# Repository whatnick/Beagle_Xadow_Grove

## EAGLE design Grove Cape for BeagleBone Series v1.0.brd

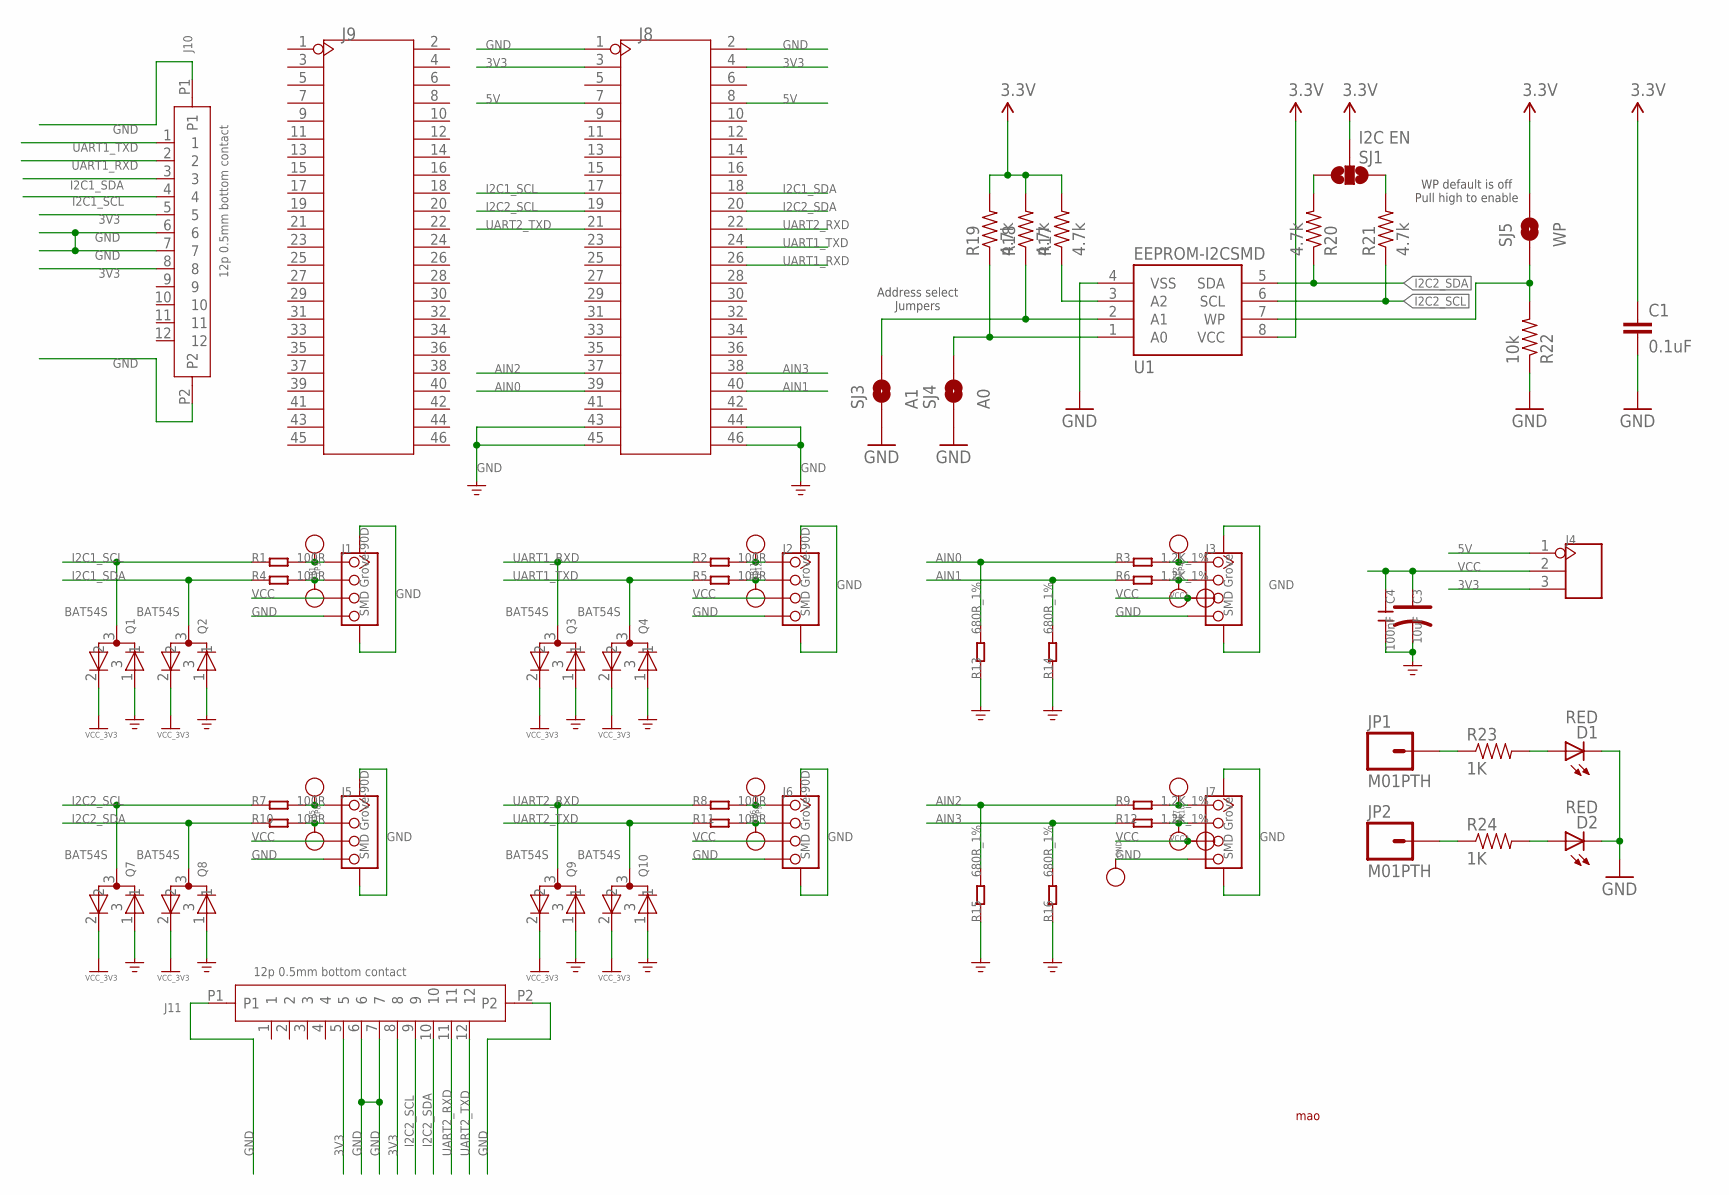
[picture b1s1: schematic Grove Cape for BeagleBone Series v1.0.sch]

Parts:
C1: 0.1uF; 0603-CAP
C3: 10uF; AVX-A
C4: 100nF; C0603
D1, D2: RED; LED-0603
GND: PAD-TEST-POINT'4545'; TP_4545
J1, J2, J5, J6: SMD Grove-90D; 4P-SMD-2.0
J3, J7: SMD Grove; 4P-SMD-2.0
J4: HEADER-3P-2.54; 3P-2.54
J8, J9: HEADER-2X23P; 2X23P-2.54
J10, J11: 12p 0.5mm bottom contact; 12P-0.5
JP1, JP2: M01PTH; 1X01
Q1, Q2, Q3, Q4, Q7, Q8, Q9, Q10: BAT54S; SOT23
R1, R2, R4, R5, R7, R8, R10, R11: 100R; R0603
R3, R6, R9, R12: 1.2K_1%; R0603
R13, R14, R15, R16: 680R_1%; R0603
R17, R18, R19, R20, R21: 4.7k; 0603
R22: 10k; 0603-RES
R23, R24: 1K; 0603-RES
SJ1: I2C EN; SJ_3_PASTE1&2&3
SJ3: A1; SJ_2S-NO
SJ4: A0; SJ_2S-NO
SJ5: WP; SJ_2S-NO
TP1, TP2, TP3, TP4, TP5, TP6, TP7, TP8, TP9, TP10, TP11, TP12: PAD-TEST-POINT'4545'; TP_4545
U1: EEPROM-I2CSMD; SO08
VCC1, VCC2: PAD-TEST-POINT'4545'; TP_4545

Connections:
3V3: C1.1, J4.3, J8.3, J8.4, J10.5, J10.8, J11.5, J11.8, Q1.2, Q2.2, Q3.2, Q4.2, Q7.2, Q8.2, Q9.2, Q10.2, R17.2, R18.2, R19.2, SJ1.2, SJ5.2, U1.8 (VCC)
5V: J4.1, J8.7, J8.8
A0: R19.1, SJ4.2, U1.1 (A0)
A1: R18.1, SJ3.2, U1.2 (A1)
AIN0: J8.39, R3.1, R13.2
AIN1: J8.40, R6.1, R14.2
AIN2: J8.37, R9.1, R15.2
AIN3: J8.38, R12.1, R16.2
GND: C1.2, C3.-, C4.2, D1.C, D2.C, GND.T, J1.4, J1.SS1, J1.SS2, J2.4, J2.SS1, J2.SS2, J3.4, J3.SS1, J3.SS2, J5.4, J5.SS1, J5.SS2, J6.4, J6.SS1, J6.SS2, J7.4, J7.SS1, J7.SS2, J8.1, J8.2, J8.43, J8.44, J8.45, J8.46, J10.6, J10.7, J10.P1, J10.P2, J11.6, J11.7, J11.P1, J11.P2, Q1.1, Q2.1, Q3.1, Q4.1, Q7.1, Q8.1, Q9.1, Q10.1, R13.1, R14.1, R15.1, R16.1, R22.1, SJ3.1, SJ4.1, U1.4 (VSS)
I2C1_SCL: J8.17, J10.4, Q1.3, R1.1
I2C1_SDA: J8.18, J10.3, Q2.3, R4.1
I2C2_SCL: J8.19, J11.9, Q7.3, R7.1, R21.1, U1.6 (SCL)
I2C2_SDA: J8.20, J11.10, Q8.3, R10.1, R20.1, U1.5 (SDA)
unnamed: R17.1, U1.3 (A2)
unnamed: J7.1, R9.2, TP7.T
unnamed: J7.2, R12.2, TP10.T
unnamed: J1.1, R1.2, TP1.T
unnamed: J1.2, R4.2, TP3.T
unnamed: J2.1, R2.2, TP11.T
unnamed: J2.2, R5.2, TP12.T
unnamed: J5.1, R7.2, TP5.T
unnamed: J5.2, R10.2, TP8.T
unnamed: J6.1, R8.2, TP6.T
unnamed: J6.2, R11.2, TP9.T
unnamed: J3.1, R3.2, TP2.T
unnamed: J3.2, R6.2, TP4.T
unnamed: R20.2, SJ1.3
unnamed: R21.2, SJ1.1
unnamed: R22.2, SJ5.1, U1.7 (WP)
unnamed: D1.A, R23.2
unnamed: D2.A, R24.2
unnamed: JP1.1, R23.1
unnamed: JP2.1, R24.1
UART1_RXD: J8.26, J10.2, Q3.3, R2.1
UART1_TXD: J8.24, J10.1, Q4.3, R5.1
UART2_RXD: J8.22, J11.11, Q9.3, R8.1
UART2_TXD: J8.21, J11.12, Q10.3, R11.1
VCC: C3.+, C4.1, J1.3, J2.3, J3.3, J4.2, J5.3, J6.3, J7.3, VCC1.T, VCC2.T

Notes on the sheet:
mao
WP default is off Pull high to enable
Address select Jumpers

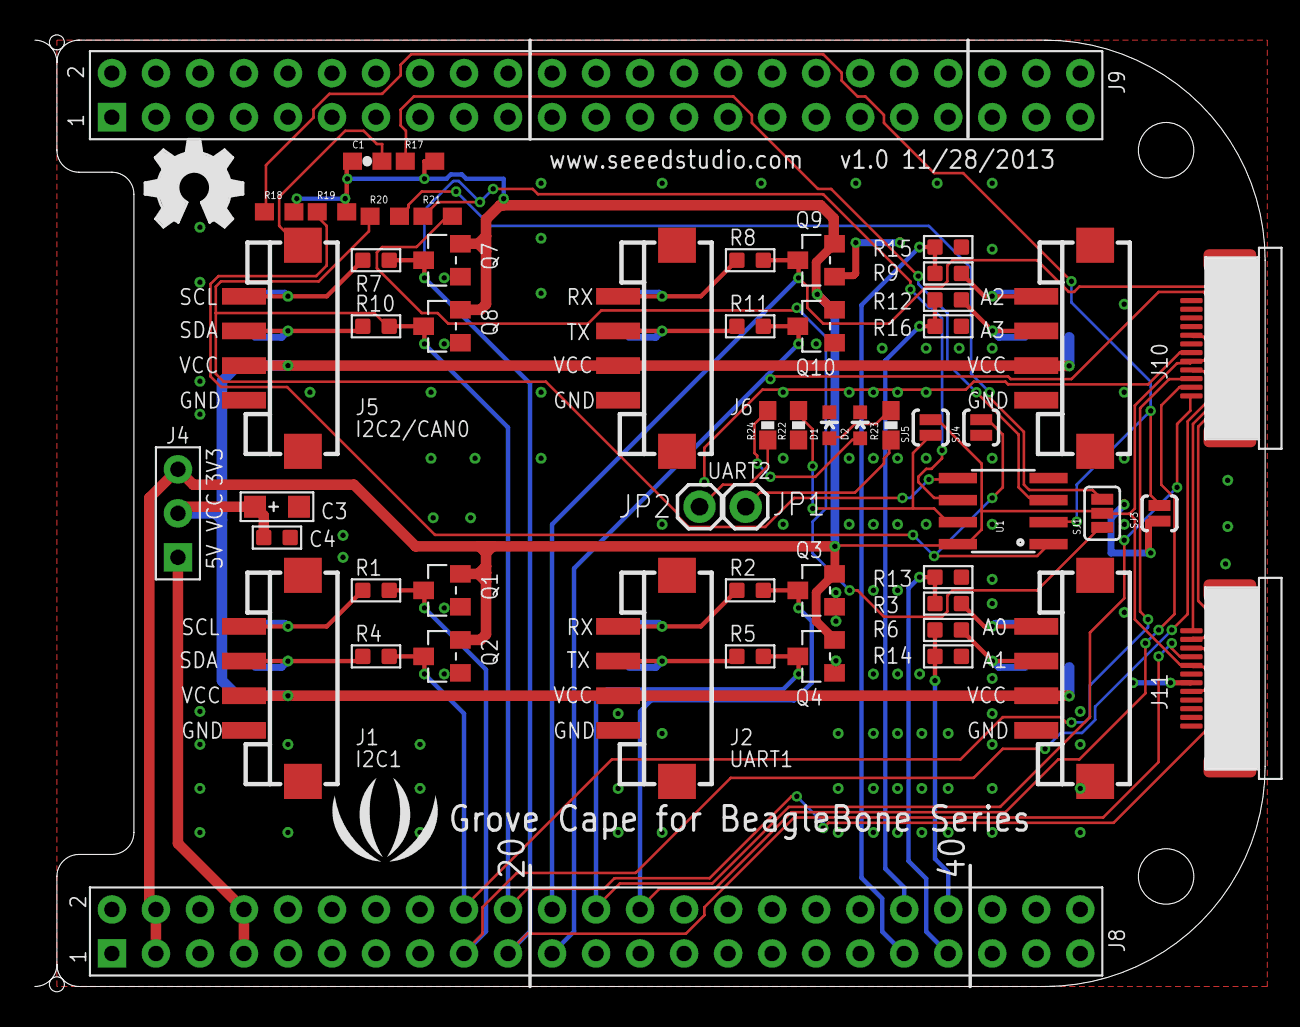
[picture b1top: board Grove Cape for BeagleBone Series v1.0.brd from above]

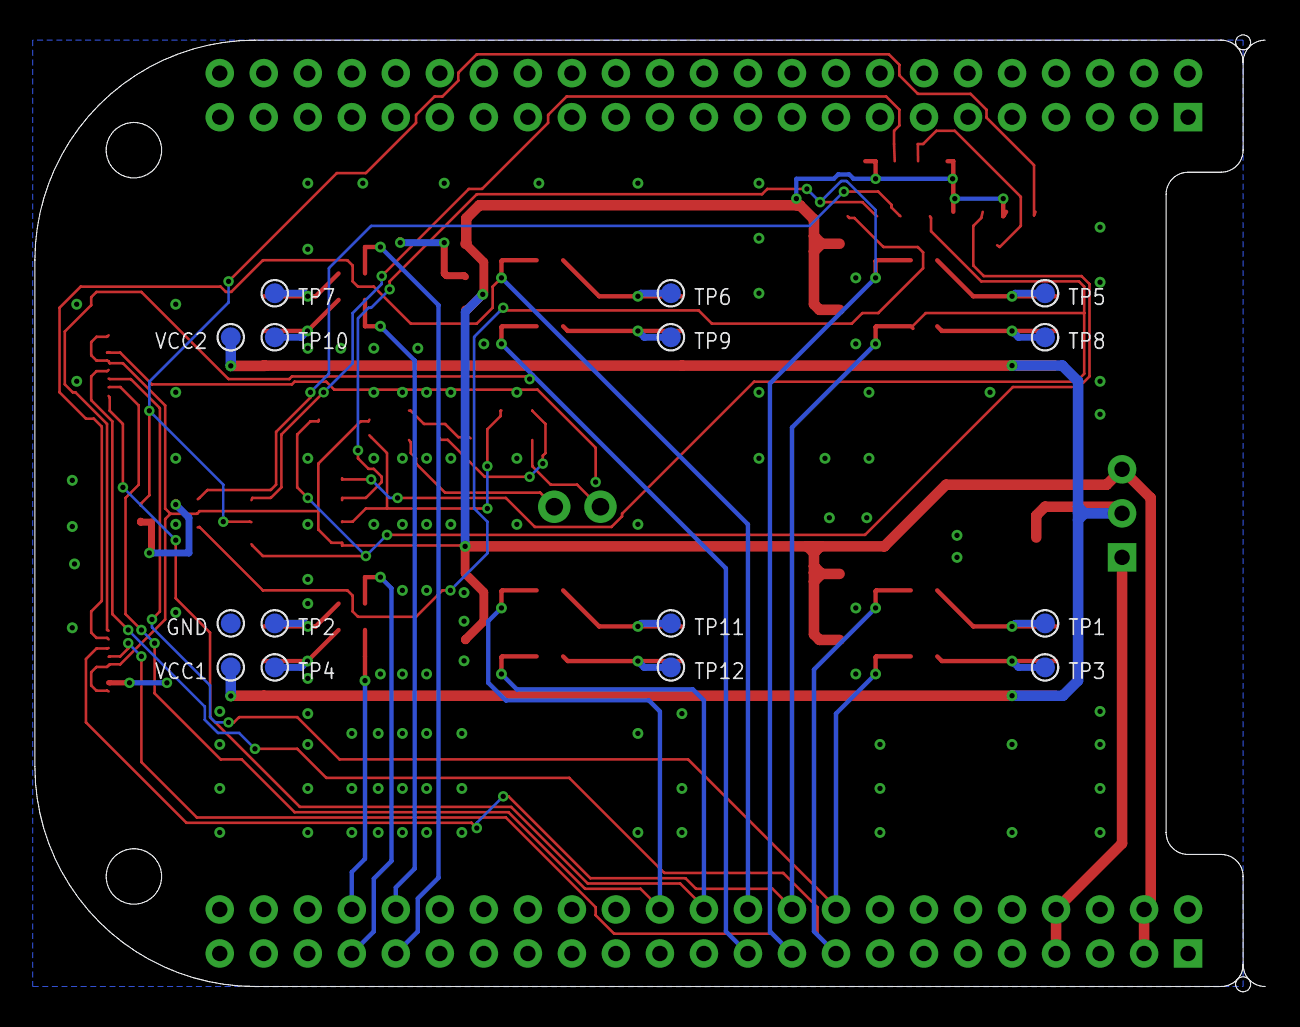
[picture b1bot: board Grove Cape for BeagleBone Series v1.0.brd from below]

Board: 2 copper layers, 71.0 x 55.2 mm, 74 parts (15 on the bottom side), 38 nets.

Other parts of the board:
U$26, U$27: HOLE-3.2/7.0
U$29: LOGO_SILK
U$33: OSHW_FILLX200_NOTEXT

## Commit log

2014-11-05 Initial import
2014-12-04 Fixed component position and silk Screen

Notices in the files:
parts and their libraries:
SparkFun-DigitalIC: Licensing: CC v3.0 Share-Alike You are welcome to use this library for commercial purposes.
SparkFun-LED: Licensing: Creative Commons ShareAlike 4.0 International - https://creativecommons.org/licenses/by-sa/4.0
